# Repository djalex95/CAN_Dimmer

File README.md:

# CAN LED Dimmer

KiCad-10-Projekt fuer einen vierkanaligen CAN-/Bluetooth-LED-Dimmer.

## Projekt oeffnen

`CAN LED Dimmer.kicad_pro` oeffnen. Bibliotheken und 3D-Modelle sind projektlokal ueber `${KIPRJMOD}` eingebunden.

## Dateien

| Datei / Ordner | Inhalt |
|---|---|
| CAN LED Dimmer.kicad_sch | Hauptblatt / Hierarchie |
| MCU - Bluetooth - CAN.kicad_sch | Controller und Kommunikation |
| Power Supply.kicad_sch | Spannungsversorgung |
| LED Outputs.kicad_sch | Ausgangsstufen |
| CAN LED Dimmer.kicad_pcb | Aktueller Layoutstand |
| CAN LED Dimmer.kicad_dru | Benutzerdefinierte Designregeln |
| CAN LED Dimmer-eagle-import.kicad_sym | Bauteilbibliothek, aus Import weiterentwickelt |
| CAN_LED_Dimmer-MCU.kicad_sym | STM32C552RET6_GROUPED |
| CAN_LED_Dimmer-layout.pretty | Projekt-Footprints |
| 3dmodels | Modelle fuer Platine und Bibliotheks-Footprints |
| sym-lib-table / fp-lib-table | Bibliothekszuordnungen |

## Weiterbearbeitung

Zielcontroller: STM32C552RET6 im LQFP64. Bibliotheksaenderungen werden nicht automatisch in bereits platzierte Symbole und Footprints uebernommen. Aktualisierungen gezielt aus den Bibliotheken uebernehmen, danach Verbindungen sowie ERC/DRC pruefen.

Das Projekt ist ein Arbeitsstand, keine Fertigungsfreigabe. Fruehere ERC-/DRC-Ergebnisse gelten nicht automatisch fuer aktuelle Aenderungen. Die Bereinigung hat weder Schaltung noch Layout geaendert.

Vier LED-Kanaele, vorgesehen ca. 5 A je Kanal und 1 kHz PWM; Versorgung 12 V, optional 24 V. Transientenfestigkeit, thermische Belastung und Signalqualitaet am fertigen Entwurf verifizieren.

Der gemeinsame ACT45B/SRF0504-Footprint hat Kupferpads fuer beide Gehaeuse, aber Pastenfenster fuer TDK. Fuer automatische Bourns-Bestueckung ist die Pastenschablone anzupassen. Die Bauteile sind elektrisch nicht identisch.

## Sicherungen

Git-Historie bleibt in `.git` erhalten. Alte lokale Dateihistorie, manuelle Sicherungen und veraltete Berichte liegen ausserhalb des Projekts unter `../KiCadProject-Archiv/`. Neue KiCad-Sicherungen weiterhin verwenden; sie wurden nicht deaktiviert.

Lokale Benutzereinstellungen (`*.kicad_prl`) bleiben erhalten und werden von Git ignoriert.

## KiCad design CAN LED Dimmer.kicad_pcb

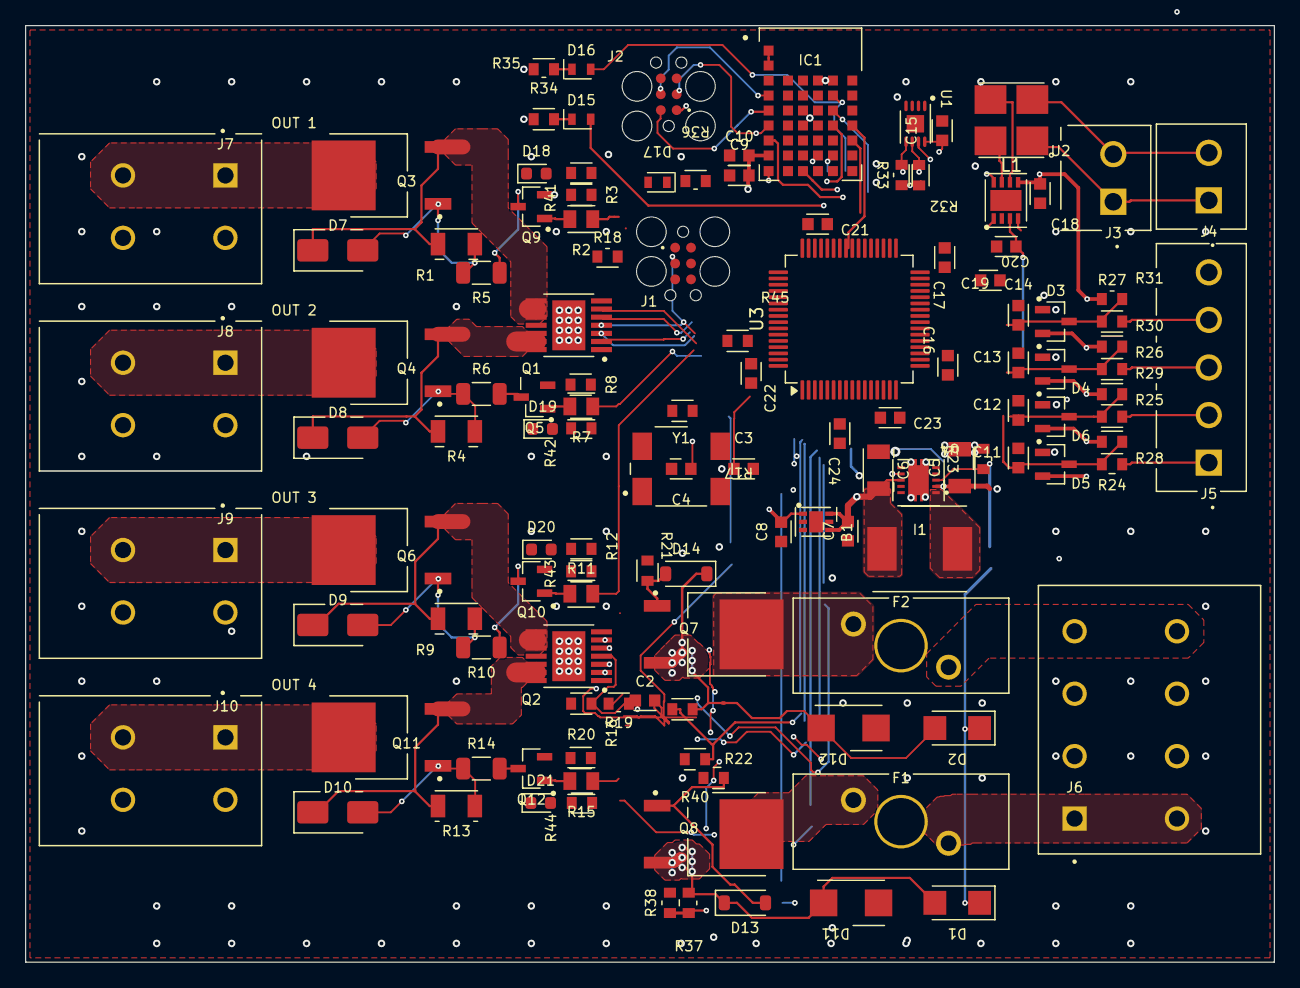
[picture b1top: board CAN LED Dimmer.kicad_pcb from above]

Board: 4 copper layers, 100.0 x 75.0 mm, 122 parts (0 on the bottom side), 97 nets.

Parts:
B1: NCP730BMT330TBG; SON65P200X200X80-7N_B1
C2: 1nF; CAPC1608X85_C2
C3: 27pF; CAPC1608X85_C3
C4: 27pF; CAPC1608X85_C4
C5: 4.7µF; CAPC3216X135_C5
C6: 47µF; CAPC3216X135_C6
C7: 1µF; CAPC1608X85_C7
C8: 1µF; CAPC1608X85_C8
C9: 1µF; CAPC1608X85_C9
C10: 100nF; CAPC1608X85_C10
C11: 100nF; CAPC1608X85_C11
C12: 100nF; CAPC1608X85_C12
C13: 100nF; CAPC1608X85_C13
C14: 100nF; CAPC1608X85_C14
C15: 100nF; CAPC1608X85_C15
C16, C22: 100nF; CAPC1608X85_C16
C17, C21, C23, C24: 100nF; CAPC1608X85_C17
C18: 100nF; CAPC1608X85_C18
C19: 100nF; CAPC1608X85_C19
C20: 2.2µF; CAPC1608X85_C16
D1: D_PMEG4010EP; SODFL4725X110N_SOD128_D1
D2: D_PMEG4010EP; SODFL4725X110N_SOD128_D2
D3: D_BAV99; SOT95P237X110-3N_D3
D4: D_BAV99; SOT95P237X110-3N_D4
D5: D_BAV99; SOT95P237X110-3N_D5
D6: D_BAV99; SOT95P237X110-3N_D6
D7: 15V BZG03C15-M3-08; D_SMA_AC_D7
D8: 15V BZG03C15-M3-08; D_SMA_AC_D8
D9: 15V BZG03C15-M3-08; D_SMA_AC_D9
D10: 15V BZG03C15-M3-08; D_SMA_AC_D10
D11: SM6T27CA; DIONM5436X265N_D11
D12: SM6T27CA; DIONM5436X265N_D12
D13: 15V BZT52C15-G3-18; D_SOD-123_AC_D13
D14: 15V BZT52C15-G3-18; D_SOD-123_AC_D14
D15: CHIP-FLAT-G_0603-0.35MM; LEDC1608X35N_FLAT-G_D15
D16: CHIP-FLAT-R_0603-0.35MM; LEDC1608X35N_FLAT-R_D16
D17: CHIP-FLAT-B_0603-0.35MM; LEDC1608X35N_FLAT-B_D17
D18: Green; LED_0603_1608Metric_D18
D19: Green; LED_0603_1608Metric_D19
D20: Green; LED_0603_1608Metric_D20
D21: Green; LED_0603_1608Metric_D21
F1: 01530008Z; 01530008_F1
F2: 01530008Z; 01530008_F2
I1: 22uH 2.6A; SMMS0630-220M_I1
IC1: 2621011024000; WIRL-BTLE_2621011024000_IC1
J1: CON_TC2030_SWD; TC2030_J1
J2: CON_TC2030_SWD; TC2030_J2
J3: CON_2P_TBP02R2-381-02BE; TBP02R2-381-02BE_J3
J4: CON_2P_TBP02R2-381-02BE; TBP02R2-381-02BE_J4
J5: CON_5P_TBP02R2-381-05BE; TBP02R2-381-05BE_J5
J6: CON_4P_1190299; 1190299_J6
J7: CON_2P_1190297; 1190297_J7
J8: CON_2P_1190297; 1190297_J8
J9: CON_2P_1190297; 1190297_J9
J10: CON_2P_1190297; 1190297_J10
L1: ACT45B-510-2P-TL003; CMC_ACT45B_SRF0504_Universal
Q1: PWR_BTS70202EPAXUMA1; SOP65P600X114-15T265X400N_Q1
Q2: PWR_BTS70202EPAXUMA1; SOP65P600X114-15T265X400N_Q2
Q3: Q_IPD50P04P413ATMA2; PG-TO252-3-313_Q3
Q4: Q_IPD50P04P413ATMA2; PG-TO252-3-313_Q4
Q5: Q_BSS138_N_CH; SOT95P237X110-3N_Q5
Q6: Q_IPD50P04P413ATMA2; PG-TO252-3-313_Q6
Q7: Q_IPD90P04P4L04ATMA2; PG-TO252-3-313_Q7
Q8: Q_IPD90P04P4L04ATMA2; PG-TO252-3-313_Q8
Q9: Q_BSS138_N_CH; SOT95P237X110-3N_Q9
Q10: Q_BSS138_N_CH; SOT95P237X110-3N_Q10
Q11: Q_IPD50P04P413ATMA2; PG-TO252-3-313_Q11
Q12: Q_BSS138_N_CH; SOT95P237X110-3N_Q12
R1: 3.3k; RESC3216X70_R1
R2: 330; RESC2012X65_R2
R3: 100k; RESC1608X60_R3
R4: 3.3k; RESC3216X70_R4
R5: 470; R_1206_3216Metric_R5
R6: 470; R_1206_3216Metric_R6
R7: 330; RESC2012X65_R7
R8: 100k; RESC1608X60_R8
R9: 3.3k; RESC3216X70_R9
R10: 470; R_1206_3216Metric_R10
R11: 330; RESC2012X65_R11
R12: 100k; RESC1608X60_R12
R13: 3.3k; RESC3216X70_R13
R14: 470; R_1206_3216Metric_R14
R15: 330; RESC2012X65_R15
R16: 100k; RESC1608X60_R16
R17: 4.7k; RESC1608X60_R17
R18: 180; RESC1608X60_R18
R19: 4.7k; RESC1608X60_R19
R20: 180; RESC1608X60_R20
R21: 100k; RESC1608X60_R21
R22: 100k; RESC1608X60_R22
R23: 56k2; RESC1608X60_R23
R24: 10k; RESC1608X60_R24
R25: 10k; RESC1608X60_R25
R26: 10k; RESC1608X60_R26
R27: 10k; RESC1608X60_R27
R28: 100; RESC1608X60_R28
R29: 100; RESC1608X60_R29
R30: 100; RESC1608X60_R30
R31: 100; RESC1608X60_R31
R32: 4.7k; RESC1608X60_R32
R33: 4.7k; RESC1608X60_R33
R34: 1k; RESC1608X60_R34
R35: 1k; RESC1608X60_R35
R36: 1k; RESC1608X60_R36
R37: 100k; RESC1608X60_R37
R38: 10k; RESC1608X60_R38
R39: 100k; RESC1608X60_R39
R40: 10k; RESC1608X60_R40
R41: 1k; RESC1608X60_R41
R42: 1k; RESC1608X60_R42
R43: 1k; RESC1608X60_R43
R44: 1k; RESC1608X60_R44
R45: 0; RESC1608X60_R30
U1: EEPROM_M24C04-FMC6TG; SON50P300X200X60-9T139N_U1
U2: TLT9251VLEXUMA1; SON65P300X300X110-9N_U2
U3: STM32C552RET6; LQFP-64_10x10mm_P0.5mm
U4: U_LM5166XDRCR; VSON-10-EP_U4
Y1: 8MHz; OSCCC720X520X130N_7X5X1.3_Y1

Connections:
+3V3: B1.1 (OUT), C8.2, C9.2, C10.2, C15.2, C16.2, C17.2, C18.2, C21.2, C22.2, C23.1, D3.2 (K), D4.2 (K), D5.2 (K), D6.2 (K), IC1.8, J1.1 (VCC), J2.1 (VCC), R24.2, R25.2, R26.2, R27.2, R32.2, R33.2, U1.8 (VCC), U2.5 (VIO), U3.13 (VREF+), U3.19 (VDD), U3.32 (VDD), U3.48 (VDD), U3.64 (VDD)
+5V: B1.4 (EN), B1.6 (IN), C6.2, C7.2, C19.2, I1.2, U2.3 (VCC), U4.8 (VOUT)
/LED Outputs/IS_A: Q1.4 (IS), R17.2, R18.2
/LED Outputs/IS_B: Q2.4 (IS), R19.2, R20.2
/LED Outputs/LED_IND_1: D18.2 (A), R41.2
/LED Outputs/LED_IND_2: D19.2 (A), R42.2
/LED Outputs/LED_IND_3: D20.2 (A), R43.2
/LED Outputs/LED_IND_4: D21.2 (A), R44.2
/LED Outputs/LED_OUT_1: J7.1 (1.1), J7.2 (1.2), Q3.3 (D)
/LED Outputs/LED_OUT_2: J8.1 (1.1), J8.2 (1.2), Q4.3 (D)
/LED Outputs/LED_OUT_3: J9.1 (1.1), J9.2 (1.2), Q6.3 (D)
/LED Outputs/LED_OUT_4: J10.1 (1.1), J10.2 (1.2), Q11.3 (D)
/LED Outputs/OUT_A0: D8.C (K), Q1.12 (OUT0_3), Q1.13 (OUT0_2), Q1.14 (OUT0_1), Q4.2 (S), R4.2
/LED Outputs/OUT_A1: D7.C (K), Q1.8 (OUT1_3), Q1.9 (OUT1_2), Q1.10 (OUT1_1), Q3.2 (S), R1.2
/LED Outputs/OUT_B0: D10.C (K), Q2.12 (OUT0_3), Q2.13 (OUT0_2), Q2.14 (OUT0_1), Q11.2 (S), R13.2
/LED Outputs/OUT_B1: D9.C (K), Q2.8 (OUT1_3), Q2.9 (OUT1_2), Q2.10 (OUT1_1), Q6.2 (S), R9.2
/MCU - Bluetooth - CAN/<NO NET>: C13.2, D4.3 (COMMON), R26.1, R30.1, U1.7 (/WC), U3.22 (PA6), U3.39 (PC8)
/MCU - Bluetooth - CAN/BLE_CTS: IC1.16, U3.44 (PA11)
/MCU - Bluetooth - CAN/BLE_LED0: D16.A, IC1.D2, U3.37 (PC6)
/MCU - Bluetooth - CAN/BLE_LED1: D15.A, IC1.D3, U3.38 (PC7)
/MCU - Bluetooth - CAN/BLE_MODE_0: IC1.11, U3.52 (PC11)
/MCU - Bluetooth - CAN/BLE_MODE_1: IC1.7, U3.53 (PC12)
/MCU - Bluetooth - CAN/BLE_RST: IC1.6, J2.3 (NRST), U3.50 (PA15)
/MCU - Bluetooth - CAN/BLE_RTS: IC1.17, U3.45 (PA12)
/MCU - Bluetooth - CAN/BLE_UART_EN: IC1.D4, U3.51 (PC10)
/MCU - Bluetooth - CAN/BTN1: J5.1, R28.2
/MCU - Bluetooth - CAN/BTN2: J5.2, R29.2
/MCU - Bluetooth - CAN/BTN3: J5.3, R30.2
/MCU - Bluetooth - CAN/BTN4: J5.4, R31.2
/MCU - Bluetooth - CAN/CAN_RX: U2.4 (RXD), U3.33 (PB12)
/MCU - Bluetooth - CAN/CAN_STBY: U2.8 (STB), U3.35 (PB14)
/MCU - Bluetooth - CAN/CAN_TX: U2.1 (TXD), U3.34 (PB13)
/MCU - Bluetooth - CAN/DIAG_LED: D17.A, U3.36 (PB15)
/MCU - Bluetooth - CAN/GPIO_BTN1: C11.2, D5.3 (COMMON), R24.1, R28.1, U3.20 (PA4)
/MCU - Bluetooth - CAN/GPIO_BTN2: C12.2, D6.3 (COMMON), R25.1, R29.1, U3.21 (PA5)
/MCU - Bluetooth - CAN/GPIO_BTN4: C14.2, D3.3 (COMMON), R27.1, R31.1, U3.23 (PA7)
/MCU - Bluetooth - CAN/I2C1_SCL: R32.1, U1.6 (SCL), U3.41 (PA8)
/MCU - Bluetooth - CAN/I2C1_SDA: R33.1, U1.5 (SDA), U3.40 (PC9)
/MCU - Bluetooth - CAN/NRST_U3: C24.1, J1.3 (NRST), U3.7 (NRST)
/MCU - Bluetooth - CAN/U3_RX: IC1.C6, U3.43 (PA10)
/MCU - Bluetooth - CAN/U3_SWCLK: J1.4 (SWCLK/TCK), U3.49 (PA14/SWCLK)
/MCU - Bluetooth - CAN/U3_SWDIO: J1.2 (SWDIO/TMS), U3.46 (PA13/SWDIO)
DEN_A: Q1.3 (DEN), U3.62 (PB9)
DEN_B: Q2.3 (DEN), U3.3 (PC14)
DSEL_A: Q1.5 (DSEL), U3.54 (PD2)
DSEL_B: Q2.5 (DSEL), U3.4 (PC15)
GND: B1.3 (GND), B1.7 (EP), C2.1, C3.1, C4.1, C5.1, C6.1, C7.1, C8.1, C9.1, C10.1, C11.1, C12.1, C13.1, C14.1, C15.1, C16.1, C17.1, C18.1, C19.1, C20.2, C21.1, C22.1, C23.2, C24.2, D3.1 (A), D4.1 (A), D5.1 (A), D6.1 (A), D11.1, D12.1, D18.1 (K), D19.1 (K), D20.1 (K), D21.1 (K), IC1.3, IC1.9, IC1.20, IC1.B3, IC1.B4, IC1.C1, IC1.C3, IC1.C4, IC1.D1, J1.5 (GND), J2.5 (GND), J5.5, J6.3 (2.1), J6.4 (2.2), J6.5 (3.1), J6.6 (3.2), J7.3 (2.1), J7.4 (2.2), J8.3 (2.1), J8.4 (2.2), J9.3 (2.1), J9.4 (2.2), J10.3 (2.1), J10.4 (2.2), Q1.1 (GND), Q2.1 (GND), Q5.2 (S), Q9.2 (S), Q10.2 (S), Q12.2 (S), R3.1, R8.1, R12.1, R16.1, R18.1, R20.1, R21.1, R22.1, R23.1, R34.1, R35.1, R36.2, R38.2, R40.1, R45.1, U1.2 (E1), U1.3 (E2), U1.4 (VSS), U1.9 (GND), U2.2 (GND), U2.9 (EP), U3.12 (VREF-), U3.18 (VSS), U3.31 (VSS), U3.47 (VSS), U3.63 (VSS), U4.5 (RT), U4.9 (HYS), U4.10 (GND), U4.11 (EP_1), U4.12 (EP_2), U4.13 (EP_3), U4.14 (EP_4), U4.15 (EP_5)
IN0_A: Q1.2 (IN0), U3.59 (PB7)
IN0_B: Q2.2 (IN0), U3.1 (PE2)
IN1_A: Q1.6 (IN1), U3.61 (PB8)
IN1_B: Q2.6 (IN1), U3.2 (PC13)
IS_A_ADC: R17.1, U3.10 (PC2)
IS_B_ADC: C2.2, R19.1, U3.11 (PC3)
unnamed: D15.C, R34.2
unnamed: D16.C, R35.2
unnamed: D17.C, R36.1
unnamed: IC1.1, IC1.2
unnamed: IC1.4, J2.4 (SWCLK/TCK)
unnamed: IC1.5, J2.2 (SWDIO/TMS)
unnamed: J3.1, J4.1, L1.1
unnamed: J3.2, J4.2, L1.2
unnamed: F1.1, J6.1 (1.1), J6.2 (1.2)
unnamed: F2.1, J6.7 (4.1), J6.8 (4.2)
unnamed: D7.A, Q3.1 (G), R1.1, R5.1
unnamed: D8.A, Q4.1 (G), R4.1, R6.1
unnamed: Q5.3 (D), R6.2
unnamed: Q5.1 (G), R7.2
unnamed: D9.A, Q6.1 (G), R9.1, R10.1
unnamed: F2.2, Q7.3 (D)
unnamed: D14.A, Q7.1 (G), R21.2
unnamed: F1.2, Q8.3 (D)
unnamed: D13.A, Q8.1 (G), R22.2
unnamed: Q9.3 (D), R5.2
unnamed: Q9.1 (G), R2.2
unnamed: Q10.3 (D), R10.2
unnamed: Q10.1 (G), R11.2
unnamed: D10.A, Q11.1 (G), R13.1, R14.1
unnamed: Q12.3 (D), R14.2
unnamed: Q12.1 (G), R15.2
unnamed: L1.4, U2.7 (CANH)
unnamed: L1.3, U2.6 (CANL)
unnamed: IC1.D6, U3.42 (PA9)
unnamed: C3.2, U3.5 (PH0), Y1.3
unnamed: C4.2, U3.6 (PH1), Y1.1
unnamed: R45.2, U3.60 (PH2/BOOT0)
unnamed: C20.1, U3.30 (VCAP)
unnamed: R23.2, U4.3 (ILIM)
unnamed: I1.1, U4.1 (SW)
PWM_0: R2.1, R3.2, R41.1, U3.55 (PB3)
PWM_1: R7.1, R8.2, R42.1, U3.56 (PB4)
PWM_2: R11.1, R12.2, R43.1, U3.57 (PB5)
PWM_3: R15.1, R16.2, R44.1, U3.58 (PB6)
VIN1_ADC: R37.2, R38.1, U3.8 (PC0)
VIN2_ADC: R39.1, R40.2, U3.9 (PC1)
V_IN_A: D1.A, D11.2, D13.C (K), Q1.15 (VS), Q8.2 (S), R37.1
V_IN_B: D2.A, D12.2, D14.C (K), Q2.15 (VS), Q7.2 (S), R39.2
V_MCU: C5.2, D1.C (K), D2.C (K), U4.2 (VIN), U4.7 (EN)
